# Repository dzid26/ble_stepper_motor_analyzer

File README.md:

# BLE STEPPER MOTOR ANALYZER

As for June 2023, a productized version of a BLE Stepper Motor analyzer that is based on the reference design here is **available for purchase from Vector 3D**, a third party, and should be compatible with the firmware and software here. If you encounter technical difficulties, it's ok and even encouraged to ask here, and we will do our best to help on a voluntarily base and without any guarantee.

https://vector3d.co.uk/product/stepper-motor-analyser/

------

<p align="center">
  <br>
  The analyzer device of the reference design here<br>
  
</p>

<p align="center">
  The analyzer's app<br>
  
</p>

**A short video** of the app is available here https://vimeo.com/798169140

---
- [BLE STEPPER MOTOR ANALYZER](#ble-stepper-motor-analyzer)
  - [Description](#description)
  - [Design Highlights](#design-highlights)
  - [How does it work?](#how-does-it-work)
  - [Specification](#specification)
  - [Installing the device in your 3D printer](#installing-the-device-in-your-3d-printer)
  - [Using the Analyzer app.](#using-the-analyzer-app)
    - [Running the Analyzer app using a provided binary](#running-the-analyzer-app-using-a-provided-binary)
    - [Running the Analyzer app using the Python source files](#running-the-analyzer-app-using-the-python-source-files)
    - [Understanding the Analyzer app screen](#understanding-the-analyzer-app-screen)
    - [The Analyzer app buttons](#the-analyzer-app-buttons)
    - [Analyzer app command line flags](#analyzer-app-command-line-flags)
  - [Updating the firmware](#updating-the-firmware)
  - [Building your own device](#building-your-own-device)
  - [Antenna selection](#antenna-selection)
  - [Connectors](#connectors)
  - [3D Models](#3d-models)
  - [Troubleshooting connection issues](#troubleshooting-connection-issues)
  - [Hardware design files](#hardware-design-files)
  - [Firmware development](#firmware-development)
  - [Analyzer App Python development](#analyzer-app-python-development)
  - [FAQ](#faq)

---

## Description

The BLE Stepper Motor Analyzer ('the analyzer') is a low-cost, open source system that analyzes stepper motor signals and display the the data in real time on a computer screen. The system includes two parts:

1. **The Stepper Motor Probe** ('the device'). This is a small electronic board that monitors the currents through the stepper motor wires, extracts information such as steps, and speed, and transmits the data via Bluetooth BLE.

2. **The Analyzer App** ('the app'). This is a Python program that runs on a Windows, MaC OSX, or Linux PC, and displays the stepper information in real time in a graphical view.

The following block diagram shows how the device and the app related to the controller and stepper motor of an existing system such as a 3D printer. 

<p align="center">
 System Block diagram<br>
  
</p>

## Design Highlights
* The device is passive and does not interfere with the operation of the stepper motor, regardless if it is in use or turned off. Furthermore, the stepper signals are galvanically isolated from the electronics.
* Embedding the device in a 3D printer is simple. It has a small footprint, operates on 7-30 VDC, and can use a small external sticker antenna that overcomes shielding by the printer enclosure.
* The design is in the public domain (Creative Commons CC0) and can be used also commercially. Attribution and code sharing are not required.
* The device design is low cost and can be ordered fully assembled from JLCPCB or similar services.
* The device firmware can upgraded by users using a standard USB cable, no tools or adapter required.
* Each device has its fixed unique address such that multiple devices can be used and addressed independently (e.g. one for each stepper motor in your printer).
* Open BLE and Python APIs supports custom monitoring apps, such as specialized analyzers or mobile apps.

## How does it work?
The device contains two galvanic isolated current sensors that sense the currents through the two stepper coils. These values are measured 40,000 times a second and firmware on the device analyzes them and extracts information such as step count, speed, and current patterns. A Bluetooth BLE radio then transmits the data to the app which displays it in a graphical form.

 <p align="center">
 Device Block diagram<br>
  
</p>

## Specification

Item | Specification
:------------ | :-------------
Power consumption | 7-30 VDC, 1W.
Firmware update connector | USB Type C.
SOIC Module | ESP32-WROOM-32U-N4.
Current measurement | +/-2.5A per coil.
PCB | 39mm x 43mm, two layers.
Antenna  | 2.4Ghz external antenna IPX IPEX connector.
Simultaneous connections | 1 max.
Protocol | BLE 4.1 or higher, with Data Length Extension feature.
Current sensors | CC6920BSO-5A
Zero calibration | Using onboard button.
Count direction | User selected (doesn't change motor direction).
Sampling rate | 40Khz per channel.
Sampling resolution | 12bits.
Current accuracy | estimated at +/- 2%.
Max step rate | 5K full steps/sec.
Step resolution | 1/100th of a full step.
Firmware programming language | C++
Firmware programming IDE | VSCode, Platformio, ESPIDF framework.
Firmware debugging | Via optional 10 pins JTAG connector.
Electronic design tool | Kicad.
Mechanical design tool | Onshape.
Open source license | Creative Commons CC0.

## Installing the device in your 3D printer

1. Print a device carrier using a 3D printer (STL model included here) and attach the device to the carrier using two pieces of 3M VHB 1mm sticky tape or similar.
2. Attach the device carrier to the 3D printer using an additional piece of 3M VHB tape.
3. Connect the external antenna and attach the antenna to the outside of the printer.
4. Connect the motor driver and stepper motor to the two connectors as shown in the wiring diagram below. The two connectors form a path through path, such that one pair of adjacent pins are used for one coil and the other pair for the second coil.
5. Connect 7-30VDC power to the VIN connector of the device. Pay attention to polarity, though the device will not get damaged by reverse polarity. 
6. Do not connect anything to the USB connector. This connector is intended for firmware flashing only.
7. The device installation is complete. You can use your 3D printer just as you did before, regardless if the analyzer app is active or not. To monitor the stepper while your printer is turned on, use the provided analyzer app on your Windows, Mac, or Linux PC as described below. 

&nbsp;

<p align="center">
  Wiring Diagram<br>
  
</p>

## Using the Analyzer app.

### Running the Analyzer app using a provided binary
The simplest way to run the analyzer app on your computer is to look for an  executable file for your system under the 'release' directory in this repository. They also released as 'release.zip' file.

> **_NOTE:_**  The single binary files are created from the app's Python code using the Pyinstaller tool and the scripts in the python/pyinstaller directory.

### Running the Analyzer app using the Python source files
If a single app binary is not available for your system, or if you prefer to run the Python code directly, you will first need to do a few preparation to satisfy the prerequisites of the Python code.

1. Install Python on your computer. Prefer the latest stable version.
2. Clone the repository on your computer or download and extract the 'python.zip' release file.
3. Install the required python modules by running this command the 'python' directory :
   
```
pip install -r requirements.txt
```
4. Make sure that your analyzer device is powered on and start the app using the command

```
python analyzer.py
```

> **_NOTE:_**  When the device is idle, its LED blink at a rate of about 1 blink per second. When connected to the app, it blink faster about 3 blinks per second. The app can connect to a device only when it's idle as indicated by the slower blink rate.

### Understanding the Analyzer app screen

The apps screen contains the following graphs

* [A]. A rolling chart with distance in steps. Updated 50 times a second.
* [B]. A rolling chart with speed in steps/sec. Updated 50 times a second.
* [C]. A rolling chart with stepper absolute current in Amps. Updated 50 times a second. The absolute current of a stepper is sqrt(A^2 + B^2) where A and B are the momentary currents of coils A, B respectively.
* [D] A histogram of current vs speed that shows how well the driver is able to maintain the stepper current at various speeds. High coil inductance of low power voltage result in significant current level at higher speeds.
* [E] A histogram that shows the relative time spent in each speed range.
* [F] A histogram that shows the relative distance done in each speed range.
* [G] A phase (Lissajous curve) graph that shows the 'cleanliness' of the sine/cosine current signals the driver sends to the motor.
* [H] An oscilloscope graph that shows current samples from the two coils. During stepper movement in a constant speed, they should look like sine/cosine waves. 

> **_NOTE:_**  In the oscilloscope graph, a single sine or cosine cycle represents 4 stepper full steps, as shown in the graph below.

### The Analyzer app buttons
The Analyzer app contain the button listed below. 

> **_NOTE:_**  The buttons affect the app only and do not interfere with the operation of the motor.

* **Toggle Dir** - Click to change the direction of step counting.
* **Reset Data** - Click to clear the histograms and step count.
* **Time Scale X** - Click to toggle the sampling time of the signals shown in the phase graph [G] and oscilloscope graph [H] to match the movement speed. As a rule of thumb, you want to have at least one full sine/cosine wave, with higher values for slower stepper movements.
* **Pause** - Click to pause/resume the display. Useful examine interesting captured data.

> **_NOTE:_** The graphs are implemented using pyqtgraph and thus provide additional functionality that is accessible by a right mouse click on the graphs.

### Analyzer app command line flags

**--help** Prints a list with the available flags.

**--scan** The analyzer will scan for BLE devices for a few seconds, print a list of  devices it found and exit. This intended for diagnostics. The stepper motor analyzer devices have names that look like <si>STP-0C8B95F2B436</i>.

```
python analyzer.py --scan
```

**--device** Instructs the analyzer to not search on start for available devices, and instead, connect to the device with given name directly. If you set in the device a nick name using the --set-nickname flag below, you can also use that nickname as a value of the --device falg. 

```
python analyzer.py --device "STP-0C8B95F2B436"

python analyzer.py --device "X-AXIS"
```

**--set_nickname** Running the analyzer with this flags sets on the device a user friendly nickname that can be used as an alternative value for the *--device* flag. That nickname is also shown in the title of the Analyzer graphical view.

```
python analyzer.py --set_nickname "X-Axis"
```

**--max-amps** If you monitor a low current stepper motor such as a 600ma extruder motor, you can use this flag to limit the range of the current display in the Phase and Oscilloscope graphs, to zoom in on details.
```
python analyzer.py --max-amps 0.8
```

***--units*** The default units for stepper distance or rotation are full steps. You can use this flag to display other units such as mm, degrees, or extrusion mm^3. 
```
python analyzer.py --units "mm"

python analyzer.py --units "degrees"

python analyzer.py --units "mm^3"
```

**--steps_per_unit** If you are using the **--units** flag, use this flag to specify the number of full motor steps that correspond to one unit. For example, if your extruder esteps value is 540 micro steps per mm, with 16 microsteps per full step, specify the flags below:
```
python analyzer.py --units=mm --steps_per_unit 33.75
```

## Updating the firmware

To flash a firmware version follow these steps.

1. Download the release.zip file of the desired release and extract it.
2. Disconnect the power connector of the device and connect it to your computer using a USB cable.
3. Run the flash script for your Windows, Mac or Linux computer. For example:
```
flash.bat
```
 4. Verify that the the script completed with no errors and that the LED on the device is blinking at about one blink per second. The device with the new firmware is ready.

## Building your own device

1. Order assembled boards (recommended), or just order bare PCBs and assemble the components yourself. Production files for JLCPCB PCB, including for the SMT service are included in this repository.
2. Connect the device to a computer via a USB cable and notice that one LED turn on solid to indicate 3.3V power.
3. Flash the device with firmware as explained above.
4. Calibrate the current sensors for zero level by long pressing the switch until the second LED will blink 3 times to indicate that the calibration values were saved in the non volatile memory.
5. Connect an antenna, run an analyzer program as explain above and that you see some signals from the device. The LED on the device will blink faster to indicate an active connection.
6. The device is now ready for installation in the 3D printer or for shipping to your customers.

* **Schematic**: https://github.com/zapta/ble_stepper_motor_analyzer/blob/main/hardware/stepper_monitor.pdf
* **JLCPCB production files**: https://github.com/zapta/ble_stepper_motor_analyzer/tree/main/hardware/JLCPCB

> **_NOTE:_**  Resistor R16 acts as a jumper and allows to disconnect the 3.3V supply from the rest of the electronics. This is useful when diagnosing power issues.

## Antenna selection

The external antenna should  satisfy these requirements:
* Specified for the Bluetooth band of 2.4GHZ.
* Having a connector that match the ESP32 WROOM module. The connector has several names including IPEX, U.FL, or MHF1, but it's easier to distinguish it by its wider body.

<p align="center">
  Inexpensive Aliexpress sticker antennas.<br>
  
</p>

## Connectors

* **Stepper Motor Connectors** - KF2510 connector 2.54mm pitch, female, 4 wires.
* **Vin connector** - Dupont 2.54mm pitch, female, 2 wires. 

## 3D Models

3D Models of the carrier and a cover for shipping are available at https://github.com/zapta/ble_stepper_motor_analyzer/tree/main/3D

## Troubleshooting connection issues

The analyzer requires on the PC side support for Bluetooth BLE 4.1 or higher with support for the Data Length Extension feature. It is expected that most computer come with a built in adapters that support
this standard, but we also observed a very low cost BeeLink mini computer that came with an old internal Bluetooth adapter that doesn't support this standard.

The workaround in this case is to **disable the internal Bluetooth adapter** and use an **external USB Bluetooth adapter** that has an external antenna for better range. For example we had good result with this adapter that as of 2023 cost about $15 https://www.amazon.com/gp/product/B09KGVFX1K, which is based on the RTL876B chip.

> **_NOTE:_**  Installing a RTL876B based adapter on Ubuntu requires a minor tweak of the firmware file names as explained at https://fosspost.org/fix-bluetooth-rtl8761b-problem-on-linux-ubuntu-22-04/. Also, 

The symptoms of a PC bluetooth adapter that doesn't support the required protocol are that the device shows up when running *analyzer --scan* but when running the analyzer without the *--scan* flag, it fails to connect to the device.  For the more technical readers, a discussion on this topic is available here https://github.com/hbldh/bleak/issues/1227#issuecomment-1435708347

## Hardware design files

The Kicad source files and the generated JLCPCB production files are available under the *kicad* directory of this repository. As of Mar 2023, we are using Kicad 7.0, and the built in plugins **Fabrication Toolkit** and **Interactive Html Bom**.

## Firmware development

This list below outlines the steps to set up your own firmware development environment.

1. Install Visual Studio Code (VSC).
2. In Visual Studio Code, enable the <i>platformio</i> extension.
3. Download or clone this git repository on your computer.
4. In VSC, select <i>File | Open Folder</i> and select the 'platformio' directory.
5. Connect a device to your computer using a USB cable. This will create a serial port on your computer.
6. Click on the platformio <i>Upload</i> icon at the bottom of the screen (right arrow icon) and platformio will automatically install all the dependencies, build the project, and upload it to your device via the serial port.  
7. For more information on how to use platformio, check http://platformio.org.

> **_NOTE:_**  For optional hardware debugging (breakpoints, single step, etc), you will need an Espressif ESP-Prog Development Board, and to solder on your device a 10 pins JTAG connector.

> **_NOTE:_** It's OK to connect a stepper motor to the device while you develope code since the stepper signals are galvanically isolated from the USB interface and from your computer.

> **_NOTE:_** It is recommended to not connect VIN and the USB connectors at the same time to avoid ground loop, in case both the Vin power supply and your computer are grounded independently.

## Analyzer App Python development

The Analyzer's Python app is stored in the 'python/analyzer' directory and uses a library at python/common. The app is based on Bleak (BLE client) PyQtGraph (a graphing library) and uses asyncio for non blocking background operation. The list of requires python modules is in requirements.txt and they can be installed using the command

```
pip install -r requirements.txt
```

## FAQ

**Q**: This is an exciting project, can I help?

A: Of course, contribution of code, documentation, test programs or ideas are welcome.

---

**Q**: I want to monitor multiple motors in my 3D printer. Is it possible?

**A**: Of course. Simply install a device for each stepper motor you want to monitor. 

---

**Q**: I am using multiple devices, how can I select which one I connect to? 

**A**: Each device has a fixed unique name such STP-0C8B95F2B436. When you run the analyzer app, it will allow you to select a device, if more than one are available, or you can use the --device flag to force a specific device.

---

**Q**: How far can my computer be away from my 3D printer? 

**A**: Bluetooth BLE radio communication is intended for short distances of a few yards. If the radio link will not be reliable, the analyzer program will detect data gaps and will report it in its console log.

---

**Q**: Can the external antenna be eliminated to simplify installation and reduce cost? 

**A**: Yes. We believe that the ESP module ESP32-WROOM-32D-N4 which uses an internal antenna should be a drop-in replacement though we did not have the chance yet to test it.

---

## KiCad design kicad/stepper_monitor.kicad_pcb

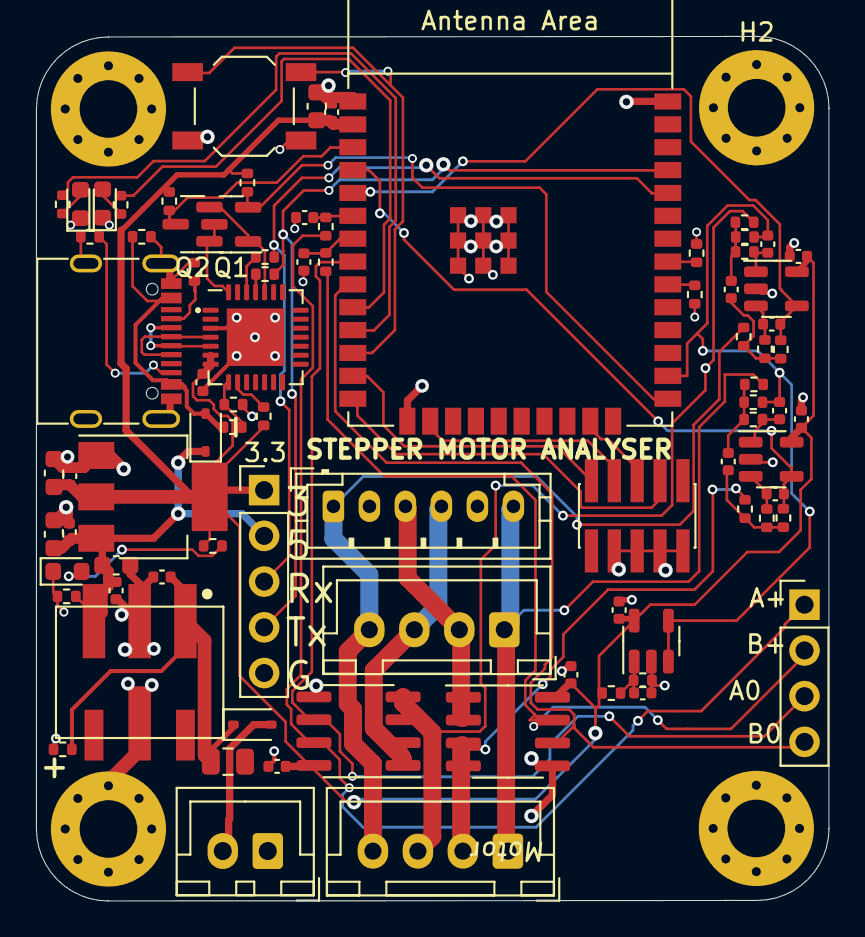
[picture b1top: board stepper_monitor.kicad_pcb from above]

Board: 2 copper layers, 44.0 x 48.0 mm, 87 parts (0 on the bottom side), 56 nets.

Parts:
C1, C6, C7, C9: 10u; C_0603_1608Metric
C2, C5, C8, C10, C11, C12, C13, C14, C15, C20, C21: 100n; C_0402_1005Metric
C3: 10u 50V; C_0805_2012Metric
C4: 100n 50V; C_0402_1005Metric
C16, C17, C18, C22, C23, C25: 10n; C_0402_1005Metric
C19, C24: 2n2; C_0402_1005Metric
D1: 1N5819WS; D_SOD-323
D2: 1N4148WS; D_SOD-323
D3: RED; LED_0603_1608Metric
D4: BLUE; LED_0603_1608Metric
D5: Yellow; LED_0603_1608Metric
H1, H2, H3, H4: MountingHole; MountingHole_3.2mm_M3_Pad_Via
J1: Conn_01x02_Pin; JST_XH_B2B-XH-A_1x02_P2.50mm_Vertical
J2, J5: Conn_01x04_Pin; JST_XH_B4B-XH-A_1x04_P2.50mm_Vertical
J3: USB_C_Receptacle_USB2.0; USB_C_Receptacle_XKB_U262-16XN-4BVC11
J4: Conn_01x04_Pin; JST_PH_B6B-PH-K_1x06_P2.00mm_Vertical
J6: JTAG; PinHeader_2x05_P1.27mm_Vertical_SMD
Q1, Q2: 2N7002; SOT-23
R1, R3: DNP; R_0402_1005Metric
R2, R5, R12, R17, R20, R25, R27, R29, R35: 10K; R_0402_1005Metric
R4: 200K; R_0402_1005Metric
R6, R7, R9, R10, R14, R18, R21, R22, R23, R28: 1K; R_0402_1005Metric
R8, R11, R13, R15: 5K1; R_0402_1005Metric
R16, R19, R24, R26: 20K; R_0402_1005Metric
R31, R32, R33: 2k; R_0402_1005Metric
SW1: SW_Push; SW_SPST_TL3342
TP1: 5V_pins; PinHeader_1x05_P2.54mm_Vertical
TP2: ScopeTestPoint; PinHeader_1x04_P2.54mm_Vertical
U1: 5V; Converter_DCDC
U2: AMS1117-3.3; SOT-223-3_TabPin2
U3: ESP32-WROOM-32U-N4; ESP32-WROOM-32E
U4, U6, U9: LMV321; SOT-23-5
U5: CP2102N-A01-GQFN28; QFN-28-1EP_5x5mm_P0.5mm_EP3.35x3.35mm
U7, U8: CC6920BSO-5A; SOIC-8_3.9x4.9mm_P1.27mm

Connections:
1.65V_ref: C16.1, C22.1, R14.2, R22.2, U3.26 (IO4), U4.3 (-), U4.4
+3V3: C1.2, C2.1, C9.2, C10.2, C11.1, C12.2, C14.2, C15.1, C20.2, C21.1, R6.1, R8.2, R29.2, R33.2, R35.2, TP1.1, U2.2 (VO), U3.2 (VDD), U4.5 (V+), U5.6 (VDD), U5.7 (REGIN), U6.5 (V+), U7.8 (VCC), U8.8 (VCC), U9.5 (V+)
+5V: C5.2, C6.2, C7.2, C8.2, D1.1 (K), R5.2, TP1.2, U1.3 (OUT), U2.3 (VI)
+12V: C3.2, C4.2, D2.1 (K), R4.1, U1.1 (IN)
A1: J2.1, J4.6, J5.1, R16.2
A2: J2.2, R19.2, U8.3 (-), U8.4 (-)
A2*: J4.3, J5.2, U8.1 (+), U8.2 (+)
B1: J2.3, R24.2, U7.3 (-), U7.4 (-)
B1*: J4.4, J5.3, U7.1 (+), U7.2 (+)
B2: J2.4, J4.1, J5.4, R26.2
CFG1: R1.1, U3.30 (IO18)
CFG2: R3.1, U3.31 (IO19)
CHA: C19.1, R18.1, U3.6 (IO34)
CHA_RAW: R18.2, TP2.1, U7.7 (VIOUT)
CHA_V0: TP2.3, U3.8 (IO32), U7.6 (VZCR)
CHA_VOLT: C18.2, R21.1, U3.4 (SENSOR_VP), U6.4
CHB: C24.1, R23.1, U3.7 (IO35)
CHB_RAW: R23.2, TP2.2, U8.7 (VIOUT)
CHB_V0: TP2.4, U3.9 (IO33), U8.6 (VZCR)
CHB_VOLT: C25.2, R28.1, U3.5 (SENSOR_VN), U9.4
D+: J3.A6 (D+), J3.B6 (D+), U5.4 (D+)
D-: J3.A7 (D-), J3.B7 (D-), U5.5 (D-)
DTR: Q1.3 (D), Q2.1 (G), U5.28 (~DTR)
EN: Q2.3 (D), R29.1, U3.3 (EN)
ESP_TCK: J6.4, U3.16 (IO13)
ESP_TDI: J6.8, U3.14 (IO12)
ESP_TDO: J6.6, U3.23 (IO15)
ESP_TMS: J6.2, U3.13 (IO14)
GNDD: C1.1, C2.2, C3.1, C4.1, C5.1, C6.1, C7.1, C8.1, C9.1, C10.1, C11.2, C12.1, C13.1, C14.1, C15.2, C19.2, C20.1, C21.2, C24.2, D3.1 (K), D4.1 (K), D5.1 (K), H1.1, H2.1, H3.1, H4.1, J1.1, J3.G (GND), J3.SHLD, J6.3, J6.5, J6.7, J6.9, R1.2, R2.1, R3.2, R4.2, R5.1, R7.2, R12.1, R13.1, R15.1, SW1.1, TP1.5, U1.2 (GND), U1.5 (GND), U2.1 (GND), U3.1 (GND), U3.15 (GND), U3.38 (GND), U3.39 (GND), U4.2 (V-), U5.3 (GND), U5.29 (GND), U6.2 (V-), U7.5 (GND), U8.5 (GND), U9.2 (V-)
IO0: Q1.2 (S), R35.1, U3.25 (IO0)
LED1: R31.2, U3.11 (IO26)
LED2: R32.2, U3.10 (IO25)
unnamed: C17.1, R14.1, R16.1, R17.2
unnamed: C17.2, R19.1, R20.2, R21.2
unnamed: C23.1, R22.1, R24.1, R25.2
unnamed: C23.2, R26.1, R27.2, R28.2
unnamed: D2.2 (A), J1.2
unnamed: D3.2 (A), R31.1
unnamed: D4.2 (A), R32.1
unnamed: D5.2 (A), R33.1
unnamed: J3.A5 (CC1), R13.2
unnamed: J3.B5 (CC2), R15.2
unnamed: C13.2, R6.2, R7.1, U4.1 (+)
unnamed: R9.2, U5.25 (RXD)
unnamed: R10.2, U5.26 (TXD)
unnamed: R11.2, R12.2, U5.8 (VBUS)
unnamed: R8.1, U5.9 (~RSTb)
unnamed: C16.2, R17.1, U6.1 (+)
unnamed: C18.1, R20.1, U6.3 (-)
unnamed: C22.2, R25.1, U9.1 (+)
unnamed: C25.1, R27.1, U9.3 (-)
RTS: Q1.1 (G), Q2.2 (S), U5.24 (~RTS)
RXD0: R10.1, TP1.3, U3.34 (RXD0/IO3)
SWITCH: SW1.2, U3.12 (IO27)
TXD0: R9.1, TP1.4, U3.35 (TXD0/IO1)
VBUS: D1.2 (A), J3.VB (VBUS), R2.2, R11.1

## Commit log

2023-01-28 Added JLCPCB production files.
2023-01-28 Added esptool
2023-01-28 Changed yellow LED to green.
2023-01-28 Simplified esptool command
2023-01-28 Minor cleanup
2023-01-28 Updated TODOs
2023-01-28 Added parsing of device name and merged the scanner into the analyzer.
2023-01-28 Added analyzer.exe
2023-01-28 Minor tweaks.
2023-01-29 Moved the analyzer's src directory.
2023-01-29 Updated windows flasher.
2023-01-29 Added automatic selection of devices.
2023-01-29 Updated analyzer.exe
2023-01-29 Added scanner test program. Increased esptool speed.
2023-01-29 Added nrf snifer for wireshak.
2023-02-08 Changed solder jumper to 0 ohms resistor.
2023-02-08 Deleted obsolete Kicad files.
2023-02-09 Added 3D models
2023-02-10 Added printout of efuses.
2023-02-10 Tweaked a log message.
2023-02-11 Simplify the power supply using a diode based design.
2023-02-12 Simplified platformio.ini. Removed debug and release build targets.
2023-02-12 Simplified the directory structure of the app's python code.
2023-02-12 Renamed directory 'kicad' to 'hardware'.
2023-02-12 Renamed directory 'platformio' to 'firmware'.
2023-02-12 Deleted the nordic nrf sniffer.
2023-02-12 Cleaned up docs directory.
2023-02-12 Generated JLCPCB produciton files.
2023-02-12 Updated README.
2023-02-12 Doc work in progress.
2023-02-12 Docs.
2023-02-12 Doc in progress.
2023-02-13 Added table of content
2023-02-13 Updated doc. Created pyinstaller version.
2023-02-15 Changed LCSC part number of green LED
2023-02-16 Renamed jj5 to j5. Increased version to 1.4.2. This is one commit past order of 1.4.1 from JLCPCB.
2023-02-16 Removed references to Windows specific dependencies.
2023-02-16 Added a test for connection cleanup.
2023-02-16 Added a connection test with at exit cleanup.
2023-02-16 Updated python test programs.
2023-02-17 Made connection cleanup at exit conditional.
2023-02-17 Updated .gitignore
2023-02-17 Added write command test.
2023-02-17 Renamed test
2023-02-17 Added atexit connection cleanup
2023-02-18 Changed chrc from write to write-nr.
2023-02-18 Added block reading test.
2023-02-18 minor tweak
2023-02-18 Updated TODO.
2023-02-19 Added bluetooth core specification 4.2 (pdf)
2023-02-20 Restructured app directories
2023-02-20 Renamed analyzer.py to analyzer_main.py
2023-02-21 Cleaned up python packages.
2023-02-21 Work in progress on connection management.
2023-02-22 Addeed device side disconnection.
2023-02-22 Auto formatted connections.py
2023-02-22 Added TODO
2023-02-22 Generated a good linux binary.
2023-02-22 Added flasher for linux
2023-02-22 Rebuilt the app for windows
2023-02-22 Rebuilt firmware
2023-02-23 Minor tweaks
2023-02-23 Cleanup
2023-02-23 Minor cleanup.
2023-02-25 Upgraded to espidf 5.
2023-02-25 Added .gitattributes file
2023-02-25 Upgraded kicad to 7.0 (design version incremented to 1.4.2)
2023-02-25 Added ibom
2023-02-25 Updated TODO.txt
2023-02-25 Changed platformio.ini comments from ; to #.
2023-02-25 Added throughput test
2023-02-25 Added notes file.
2023-02-25 Updated TODO and throughput test.
2023-02-26 sdkconfig tweaks. Increase cpu speed 160 -> 240mhz
2023-02-26 Updated firmware bin files
2023-02-26 Renamed directories to kicad, platformio, and python. No other change.
2023-02-27 Cleanup graph update tasks.
2023-02-27 Cleanup graph update tasks
2023-02-27 Cleaned up the analyzer's periodic tasks.
2023-02-27 Updated TODO
2023-02-27 Regenerated firmware binaries
2023-02-27 Regenerated analyzer's windows binary.
2023-02-28 Fixed nvs write crash. Updated firmware binary files.
2023-02-28 Added scan sort
2023-02-28 Added list of available linux chip drivers
2023-02-28 Updated to full linux bt drivers (firmware files)
2023-02-28 Fixed the device sorting.
2023-02-28 Regenerated firmware binaries.
2023-03-01 Generated analyzer binary for windows
2023-03-01 Renamed 'linux' to 'ubuntu'
2023-03-01 Regenerated ubuntu analyzer.
2023-03-02 Updated ubuntu flasher.
2023-03-05 Skeleton script for mac.
2023-03-05 Test
2023-03-05 Generated mac binary.
2023-03-06 Tweaked Analyzer for Mac.
2023-03-06 Changed device lookup from by address to by name.
2023-03-06 Regenerated mac analyzer binary
2023-03-08 Created windows binary.
2023-03-08 Generated a binary for ubuntu.
2023-03-19 Added paused states queue.
2023-03-19 Changed the tasks to not block the timer handler.
2023-03-19 Updated windows binary.
2023-03-19 Changed build_on_windows from a bash script to a batch script.
2023-03-19 Added formatter config to python project
2023-03-19 Regenerated the mac binary file.
2023-03-19 Formatted the python files. No logic change.
2023-03-19 Tweaked the base line of the histograms.
2023-03-19 Rebuilt the windows binary.
2023-03-20 Added 3D models, regenerated production files (new plugin version). No electrical changes.
2023-03-20 Versioned the espressif platform.
2023-03-21 Added device version string.
2023-03-21 Cleaned up the app version string.
2023-03-21 Added 3d model for the switch.
2023-03-21 Fixed a typo.
2023-03-21 Rebuilt windows binary.
2023-03-21 Added 3D model for tactile switch.
2023-03-21 Regenerated firmware and windows binaries.
2023-03-21 Minor python app tweak. Also regenerated windows binary.
2023-03-21 Regenerated mac binary.
2023-03-21 Rebuilt firmware binary in a clean client.
2023-03-21 Generated analyzer binary for ubuntu.
2023-03-22 Updated documentation
2023-03-22 Renamed flag --device-nick-name to --device-nickname.
2023-03-22 Regenerted the windows binary.
2023-03-22 Updated the doc with external BT adapter info.
2023-03-22 Minor doc fix.
2023-03-22 Minor doc tweak.
2023-03-22 Minor doc update.
2023-03-24 Upgraded kicad 7.0.0 -> 7.0.1
2023-04-04 Added nordic sniffer
2023-04-05 Added support for device side nickname.
2023-04-05 Formmated scan output by columns
2023-04-06 Command set-nickname now uses a write with response.
2023-04-06 Removed the post set-nickname delay. Not needed since the command is now with response.
2023-04-06 Added to the scan printout of rssi
2023-04-06 Added a TODO item.
2023-04-06 Minor typo fix.
2023-04-06 Added a test program.
2023-04-06 Adapted test to use device name instead of address.
2023-04-07 Tweaked the wdt test.
2023-04-08 Fixed the atexit disconnect on widnows. Disabled WDT heatbeat.
2023-04-08 Forcing exit(0) as a workaround for Mac OSX zsh printing error messages on exit.
2023-04-09 Tweaked the atexit handling.
2023-04-09 Minor firmware cleanup around updating the ble settings.
2023-04-09 Updated the docs.
2023-04-09 Rebuilt binary for windows.
2023-04-09 Created ubuntu binary
2023-04-09 Generated firmware binaries.
2023-04-09 Rebuilt firmware binaries.
2023-04-29 V3D Edition Design
    - M3 corner holes
    - JST XH connectors
    - Match JLCPCB capabilities
    - increased board size
    - increased via size
    - adjusted tracks in some locations to match capabilities
2023-04-29 Fixed BOM errors
2023-06-02 Updated Readme and Shipping Cover
2023-06-07 Added text and link for Vector 3D's product.
2023-06-07 Simplified the Vector 3D text.
2023-06-07 Tweaked the text.
2023-06-10 V3D improvements (#1)
    - M3 corner holes
    - JST XH connectors
    - Match JLCPCB capabilities
    - increased board size
    - increased via size
    - adjusted tracks in some locations to match capabilities
2023-06-10 Moved flashing tools from releases to tools
2023-06-10 Current sensors between the connectors
2023-06-10 JLC basic part button
2023-06-11 Connected VZCR pin from CC6920BSO. Added big scope test points. Ignored local file.
2023-06-17 Rerouted everything. Basic part LEDs. 6 pin connector. Smaller footprint. Shorter routes
2023-06-17 Added 5V dupoint pins
2023-06-17 Added easily swappapble footprint Wroom with integrated antenna
2023-06-17 Using "official" espressif footprints
2023-07-10 Routed opamp for voltage measurement. Added 4th mount hole
2023-07-10 Used ESP32 with Integrated antenna
2023-07-10 Replaced Extended part transistors with basic mosfets
2023-07-10 Added 5pin uart programming header. Fixed led resistor part number. Normal switching reverse polarity diode
